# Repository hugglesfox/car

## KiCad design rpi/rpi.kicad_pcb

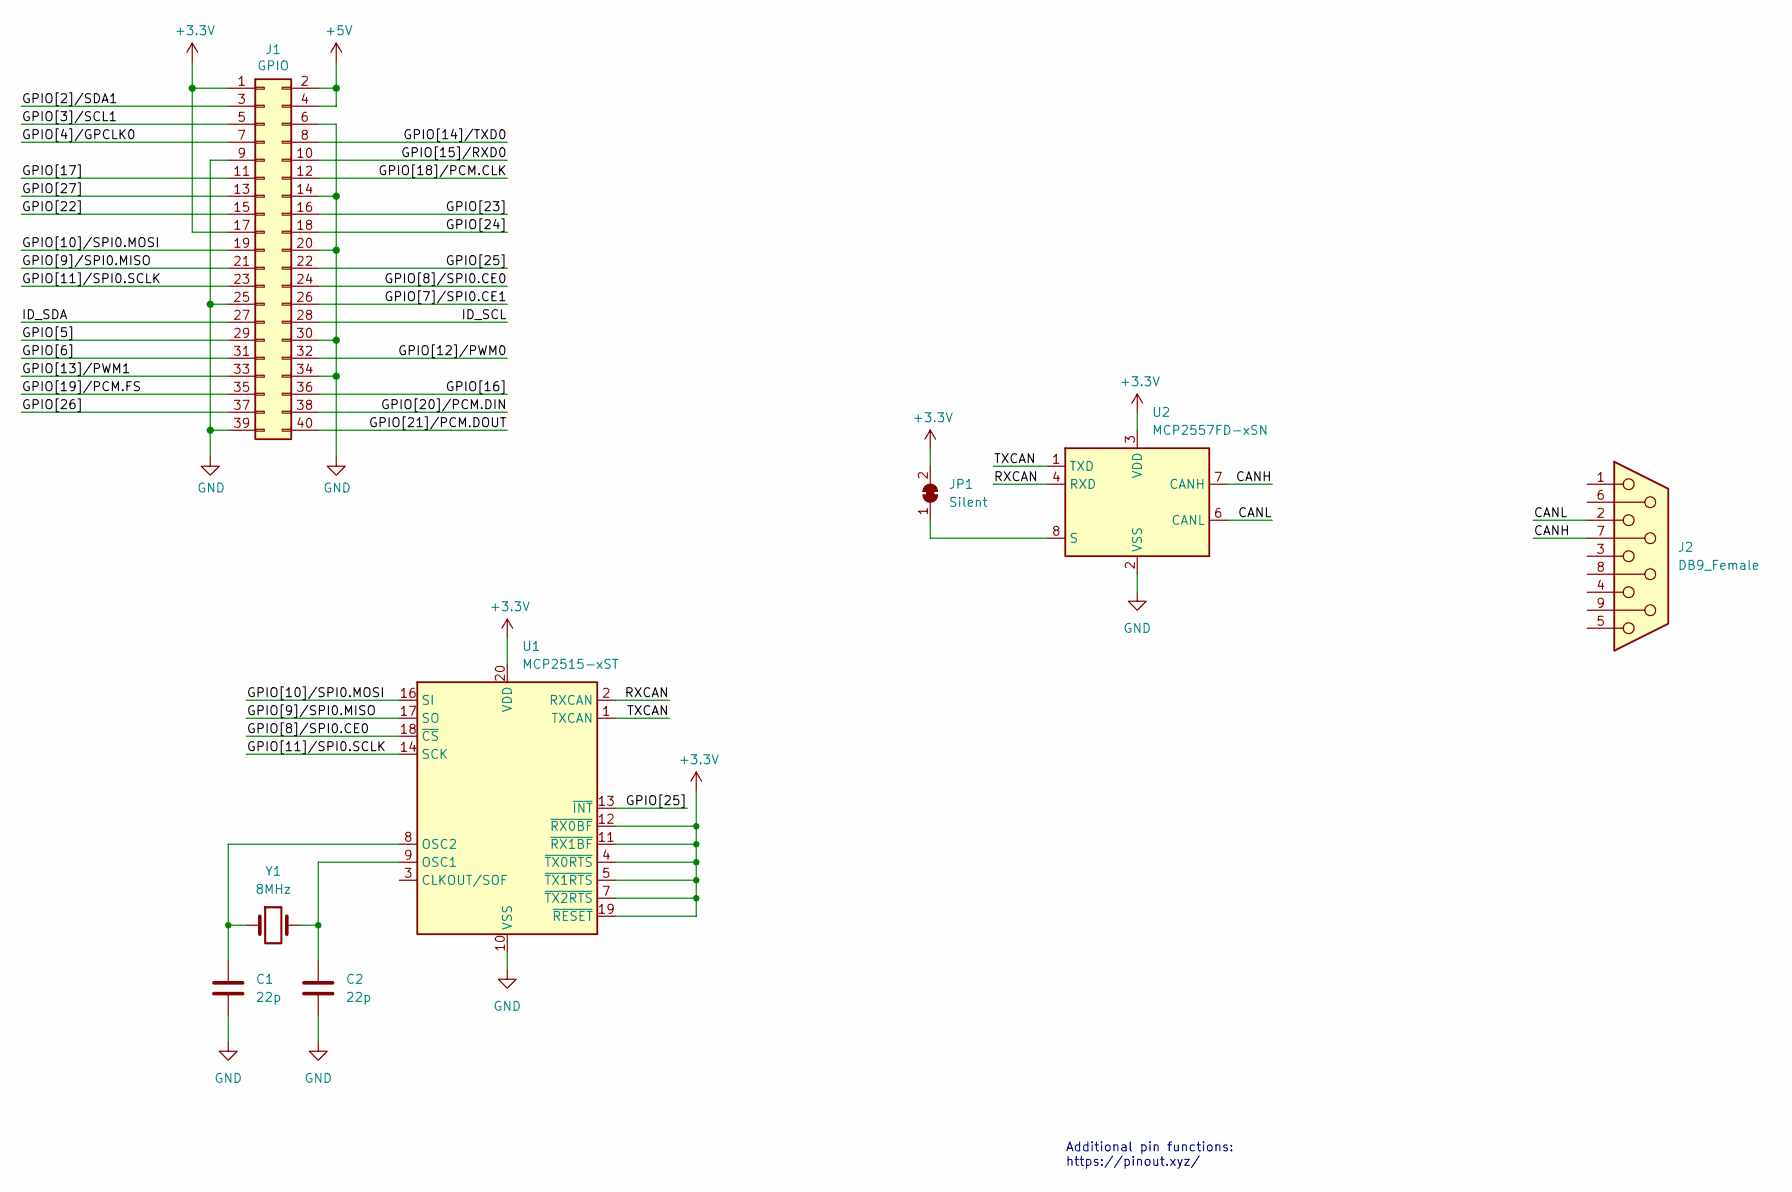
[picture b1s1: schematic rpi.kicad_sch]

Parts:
C1, C2: 22p; C_0805_2012Metric
J1: GPIO; PinSocket_2x20_P2.54mm_Vertical
J2: DB9_Female; DSUB-9_Female_Horizontal_P2.77x2.84mm_EdgePinOffset4.94mm_H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
JP1: Silent; SolderJumper-2_P1.3mm_Bridged2Bar_Pad1.0x1.5mm
U1: MCP2515-xST; TSSOP-20_4.4x6.5mm_P0.65mm
U2: MCP2557FD-xSN; SOIC-8_3.9x4.9mm_P1.27mm
Y1: 8MHz

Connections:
+3V3: J1.1, J1.17, JP1.2 (B), U1.4 (~TX0RTS), U1.5 (~TX1RTS), U1.7 (~TX2RTS), U1.11 (~RX1BF), U1.12 (~RX0BF), U1.19 (~RESET), U1.20 (VDD), U2.3 (VDD)
+5V: J1.2, J1.4
/CANH: J2.7, U2.7 (CANH)
/CANL: J2.2, U2.6 (CANL)
/GPIO[2]/SDA1: J1.3
/GPIO[3]/SCL1: J1.5
/GPIO[4]/GPCLK0: J1.7
/GPIO[5]: J1.29
/GPIO[6]: J1.31
/GPIO[7]/SPI0.CE1: J1.26
/GPIO[8]/SPI0.CE0: J1.24, U1.18 (~CS)
/GPIO[9]/SPI0.MISO: J1.21, U1.17 (SO)
/GPIO[10]/SPI0.MOSI: J1.19, U1.16 (SI)
/GPIO[11]/SPI0.SCLK: J1.23, U1.14 (SCK)
/GPIO[12]/PWM0: J1.32
/GPIO[13]/PWM1: J1.33
/GPIO[14]/TXD0: J1.8
/GPIO[15]/RXD0: J1.10
/GPIO[16]: J1.36
/GPIO[17]: J1.11
/GPIO[18]/PCM.CLK: J1.12
/GPIO[19]/PCM.FS: J1.35
/GPIO[20]/PCM.DIN: J1.38
/GPIO[21]/PCM.DOUT: J1.40
/GPIO[22]: J1.15
/GPIO[23]: J1.16
/GPIO[24]: J1.18
/GPIO[25]: J1.22, U1.13 (~INT)
/GPIO[26]: J1.37
/GPIO[27]: J1.13
/ID_SCL: J1.28
/ID_SDA: J1.27
/RXCAN: U1.2 (RXCAN), U2.4 (RXD)
/TXCAN: U1.1 (TXCAN), U2.1 (TXD)
GND: C1.2, C2.2, J1.6, J1.9, J1.14, J1.20, J1.25, J1.30, J1.34, J1.39, U1.10 (VSS), U2.2 (VSS)
unnamed: C1.1, U1.8 (OSC2), Y1.1
unnamed: C2.1, U1.9 (OSC1), Y1.2
unnamed: JP1.1 (A), U2.8 (S)

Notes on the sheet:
Additional pin functions: https://pinout.xyz/

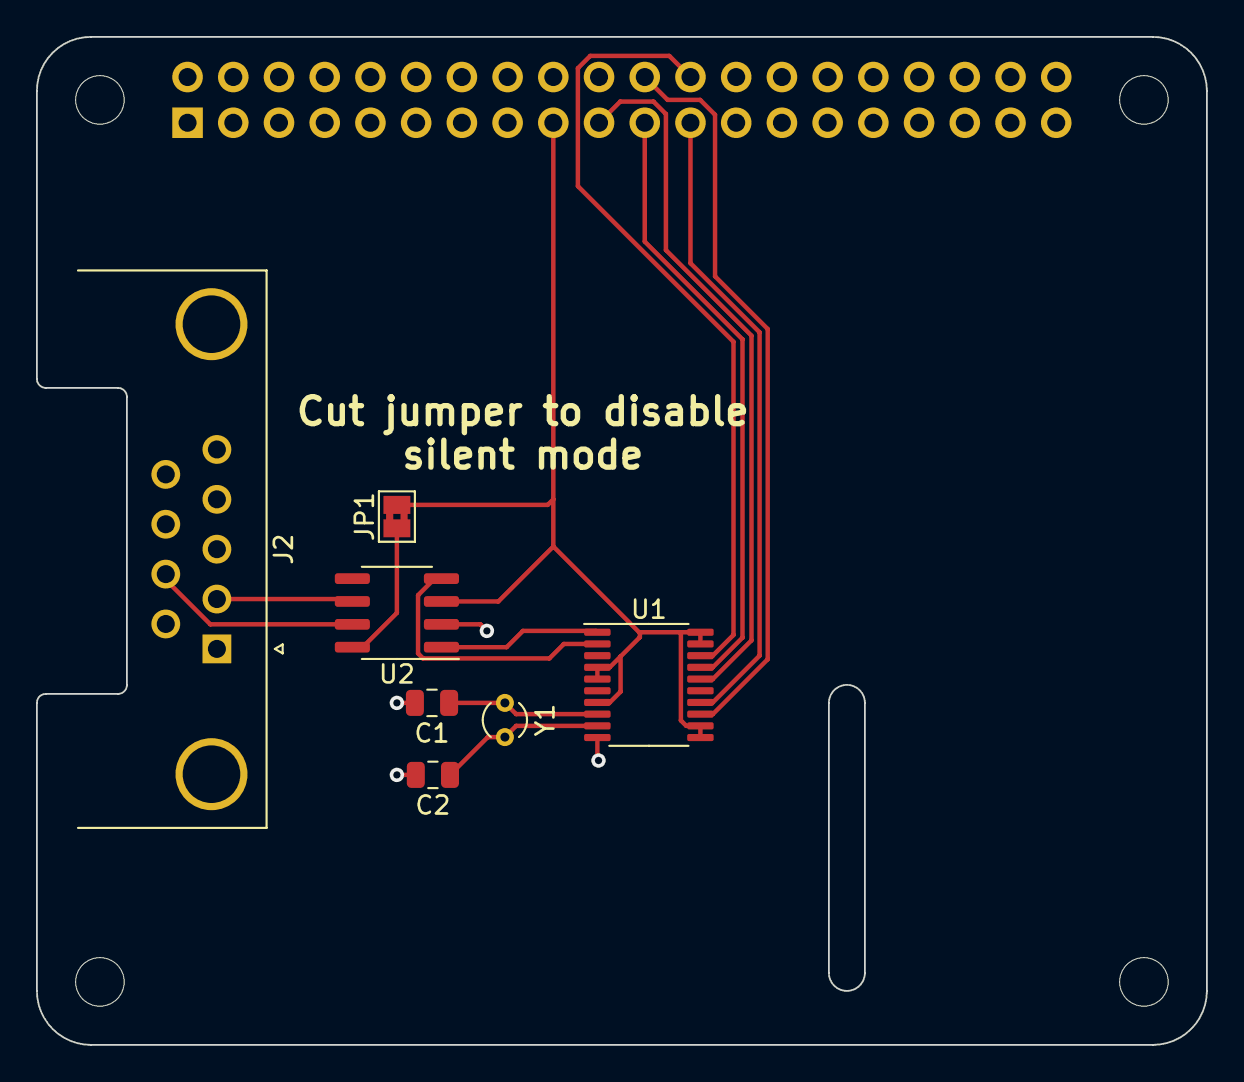
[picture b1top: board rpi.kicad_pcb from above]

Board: 2 copper layers, 65.0 x 56.0 mm, 12 parts (1 on the bottom side), 15 nets.

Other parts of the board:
MH1, MH2, MH3, MH4: MountingHole_2.7mm_M2.5

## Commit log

2023-05-01 Adjust hostname and issue
2023-05-03 Add gps configuration
2023-05-03 Restructure project to include buildroot
2023-05-03 Add build.sh
    Rather then abusing makefiles
2023-05-03 Add ca-certs
2023-05-03 Add btattach service
    To setup a serial connected bluetooth controller
2023-05-03 Move rootfs-overlay
2023-05-04 Add wifi accces point handlding
2023-05-04 Remove buildroot
2023-05-04 Add basic config
2023-05-07 Update elm327-exporter
2023-05-07 Fix dns and ntp server ip
2023-05-07 Add rfcomm systemd service
2023-05-07 Add elm327-exporter as submodule
2023-05-07 Add elm327-exporter to docker-compose
2023-05-07 Add restart always to services
2023-05-07 Add prometheus config for elm_exporter
2023-05-07 Reorganise repo
2023-05-07 Add traefik and local domain resolving
2023-05-07 Add dht11-exporter
2023-05-08 Fix typo in dhcp lease range
2023-05-16 Add config for shutdown and cabin temp sensor
2023-05-16 Fix .car resolving on IOS
2023-05-16 Add alert indicator application
2023-05-16 Add mypy to alert-indicator dev deps
2023-05-16 Fix incorrect prometheus api response parsing
2023-05-16 Change alert indicator led pin to pin 21
2023-05-16 Rename defaults to default
2023-05-16 Remove traefik and grafana
2023-05-16 Update elm-exporter
2023-05-16 Make dnsmasq start more reliably
2023-05-16 Move from dhcpcd to systemd-networkd
2023-05-16 Remove wpa2 configuration
2023-05-16 Remove traefik promethus scrape job
2023-05-16 Remove traefik labels from prometheus
2023-05-16 Remove prometheus scrape job
2023-05-16 Add a prometheus data named volume
2023-05-16 Enable systemd resolved
2023-05-22 Add rpi hat
2023-06-04 Add block diagram
2023-06-04 Add power management hardware schematics
